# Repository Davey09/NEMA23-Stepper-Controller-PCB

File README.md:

# NEMA 23 Stepper Motor Controller — Arduino-Compatible PCB

A compact, single-axis **12 V bipolar stepper motor controller** that combines an **ATmega328 microcontroller** (Arduino Uno–compatible), a **Trinamic TMC2209** silent stepper driver and an **FT232RL USB-C serial interface** on one 61 × 52 mm two-layer board.

The board is intended as a self-contained joint controller: one board drives one motor, and several boards can be networked over UART to coordinate a multi-axis machine such as a robotic arm. It was designed as the joint electronics for the [5-DOF Cycloidal Drive Robotic Arm](https://github.com/Davey09/Cycloidal-Drive-Robotic-Arm).

| Top | Bottom |
|:---:|:---:|
|  |  |

---

## Key Features

- **Arduino-compatible MCU:** ATmega328 (TQFP-32) with a 16 MHz crystal, so it can be programmed from the Arduino IDE with standard libraries such as *AccelStepper* and *TMCStepper*
- **TMC2209 stepper driver:** up to 2 A RMS, StealthChop2 silent operation, 256-step microstep interpolation and a single-wire UART configuration interface
- **Hardware current setting:** a VREF divider (R16/R17) gives a default limit of about **1.35 A RMS** with no firmware configuration needed
- **USB-C serial bridge:** FT232RL USB-to-UART with DTR auto-reset for bootloader uploads, plus TX/RX activity LEDs
- **Robust power input:** 12 V screw terminal with a US1G series diode for **reverse-polarity protection** and an NCP1117 5 V LDO for the logic rail
- **Expansion I/O:** two filtered digital and two filtered analog 3-pin headers (signal / 5 V / GND) for limit switches, encoders or sensors
- **ICSP header** for flashing the bootloader or firmware directly
- **Manual reset button** and status LEDs
- **2 × M3 mounting holes** for installation inside a joint housing or controller chassis

## Specifications

| Parameter | Value |
|---|---|
| Supply voltage | 12 V DC (motor rail), 5 V regulated logic |
| Microcontroller | ATmega328-A, 16 MHz, 5 V |
| Motor driver | TMC2209-LA (VQFN-28, thermal-via pad) |
| Motor type | 2-phase bipolar stepper (NEMA 14 / 17 / 23) |
| Default phase current | ≈ 1.35 A RMS (hardware VREF); up to 2 A RMS via UART/VREF |
| Microstepping | 1/8 hardware default (MS1 = MS2 = GND), interpolated to 1/256 |
| Chopper mode | StealthChop2 (SPREAD = GND) |
| Current-sense resistors | 0.11 Ω |
| Host interface | USB-C (USB 2.0 full speed) through FT232RL |
| Board size | 61.2 × 52.1 mm |
| Layers | 2 (F.Cu / B.Cu), 1.6 mm FR-4 |
| Components | Mostly SMD (0805 passives), through-hole connectors |
| EDA tool | KiCad 9 |

## Circuit Description

The schematic is a hierarchical design with three sheets:

| Sheet | File | Function |
|---|---|---|
| Main | `Stepper_Controller.kicad_sch` | MCU, motor driver, USB-UART, I/O headers, LEDs |
| Power input | `Power_Supply.kicad_sch` | 12 V input, reverse-polarity protection, 5 V regulation |
| Current reference | `Current_Reference.kicad_sch` | TMC2209 VREF divider |

### Power supply
The 12 V input (J6) passes through **D1 (US1G)**, which blocks current if the supply is connected backwards. The protected 12 V rail feeds the TMC2209 motor supply (VS) directly, with 4.7 µF tantalum, 100 µF and 100 nF bulk and decoupling capacitors next to the driver. An **NCP1117-5.0 LDO (U2)** produces the 5 V `VCC` rail for the MCU, the FT232RL I/O and the expansion headers.

### Microcontroller
The **ATmega328 (U1)** runs from a 16 MHz crystal (Y1) with 22 pF load capacitors and has 100 nF decoupling on each supply pin, AVCC and AREF. RESET has a 10 kΩ pull-up, a tactile reset switch (SW1) and a 100 nF DTR-coupled capacitor, so the bootloader auto-resets the same way it does on an Arduino Uno.

### Stepper driver
The **TMC2209 (U5)** is wired for STEP/DIR control from the MCU:

| TMC2209 pin | Net | ATmega328 pin | Arduino pin |
|---|---|---|---|
| STEP | `STEP` | PD7 | D7 |
| DIR | `DIR` | PD6 | D6 |
| EN (active low) | `ENA` | PD5 | D5 |
| PDN_UART | `UART` | PD2 | D2 |

- **Motor current** is set by VREF. The divider from the driver's internal 5 V output (R16 = 10 kΩ, R17 = 6.2 kΩ, filtered by C14) gives VREF ≈ 1.91 V. With 0.11 Ω sense resistors:
  `I_RMS = (VREF / 2.5 V) × 0.325 V / (R_sense + 0.02 Ω) / √2 ≈ 1.35 A`
- **Microstepping:** MS1 and MS2 are tied low, which selects 1/8 stepping with internal interpolation to 1/256 for very smooth, quiet motion.
- **SPREAD** is tied low, so the driver runs in StealthChop2 for silent operation at low and medium speeds.
- **PDN_UART** connects to an MCU pin, so firmware can override the hardware defaults over the TMC2209 single-wire UART (run current, microstep resolution, StallGuard, CoolStep).
- The motor phases (OA1/OA2, OB1/OB2) go to a 4-way 5.08 mm screw terminal (**J7**).

### USB interface
A **USB-C receptacle (J9)** with 5.1 kΩ CC pull-downs (so the board is recognised as a sink) connects to the **FT232RL (U3)**. TXD/RXD cross over to the ATmega's hardware UART (PD0/PD1), and DTR drives the auto-reset circuit. CBUS0/CBUS1 drive the TX/RX activity LEDs.

### Expansion headers and indicators
| Header | Silkscreen | MCU signal | Notes |
|---|---|---|---|
| J3 | DG_1 | D3 (PD3, INT1 / PWM) | 1 kΩ + 160 nF RC filter |
| J4 | DG_2 | D4 (PD4) | 1 kΩ + 160 nF RC filter |
| J5 | AN_1 | A0 (PC0) | 1 kΩ + 160 nF RC filter |
| J8 | AN_2 | A1 (PC1) | 1 kΩ + 160 nF RC filter |
| J2 | ISP | — | 2 × 3 ICSP programming header |

Each 3-pin header provides **signal / 5 V / GND**, so sensors and switches plug in directly. The RC filters debounce mechanical limit switches and suppress noise coupled from the motor wiring.

LEDs show 5 V power, the D13 status signal and USB TX/RX activity.

## Repository Structure

```
├── hardware/                     KiCad 9 project (open Stepper_Controller.kicad_pro)
│   ├── Stepper_Controller.kicad_pro
│   ├── Stepper_Controller.kicad_sch
│   ├── Stepper_Controller.kicad_pcb
│   ├── Power_Supply.kicad_sch
│   └── Current_Reference.kicad_sch
├── fabrication/
│   ├── Stepper_Controller_Gerbers.zip   Gerber + Excellon drill files (ready for JLCPCB / PCBWay)
│   └── BOM.csv                          Bill of materials
├── docs/
│   └── Schematic.pdf                    Full schematic, all sheets
└── images/                              3D renders
```

## Getting Started

1. **Open the design:** install [KiCad 9](https://www.kicad.org/) and open `hardware/Stepper_Controller.kicad_pro`.
2. **Order PCBs:** upload `fabrication/Stepper_Controller_Gerbers.zip` to any PCB manufacturer (2 layers, 1.6 mm, default settings).
3. **Assemble** the board using `fabrication/BOM.csv`.
4. **Burn the bootloader** through the ICSP header using *Arduino as ISP* or a USBasp, with board type **Arduino Uno**.
5. **Upload firmware** over USB-C from the Arduino IDE. A minimal test:

```cpp
#include <AccelStepper.h>

constexpr uint8_t STEP_PIN = 7, DIR_PIN = 6, EN_PIN = 5;
AccelStepper stepper(AccelStepper::DRIVER, STEP_PIN, DIR_PIN);

void setup() {
  pinMode(EN_PIN, OUTPUT);
  digitalWrite(EN_PIN, LOW);        // enable TMC2209 (active low)
  stepper.setMaxSpeed(4000);        // microsteps/s (1/8 stepping => 1600 steps/rev)
  stepper.setAcceleration(2000);
  stepper.moveTo(1600 * 5);         // 5 motor revolutions
}

void loop() {
  if (stepper.distanceToGo() == 0) stepper.moveTo(-stepper.currentPosition());
  stepper.run();
}
```

## Revision Notes (Rev A)

These items were found in design review and are planned for Rev B:

- **ICSP header mapping:** J2 pins 1 and 4 (MISO/MOSI) are joined to each other and not connected to the MCU, and pin 3 (SCK) goes to PB4 (MISO). Route J2 to PB4/PB3/PB5 as in the standard AVR 6-pin ICSP pinout.
- **FT232RL supply:** the FT232RL VCC pin (20) and the USB-C VBUS pins are not connected. Supply VCC from VBUS or the 5 V rail and add the 3V3OUT decoupling capacitor.
- **TMC2209 clock:** Y2 is a passive crystal on the CLK pin, but the TMC2209 accepts only an external clock signal or GND (internal oscillator). Tie CLK to GND and remove Y2.
- **C13 (100 µF):** this value is not practical in an 0805 package at a 16 V+ rating. Move it to a 1210 MLCC or an electrolytic footprint.

## Roadmap

- Rev B with the fixes above
- Firmware for TMC2209 UART configuration and StallGuard sensorless homing
- Multi-board UART/RS-485 network for coordinated multi-axis motion
- Optional magnetic encoder header for closed-loop position feedback

## Related Project

This controller provides the joint electronics for the **[5-DOF Cycloidal Drive Robotic Arm](https://github.com/Davey09/Cycloidal-Drive-Robotic-Arm)**.

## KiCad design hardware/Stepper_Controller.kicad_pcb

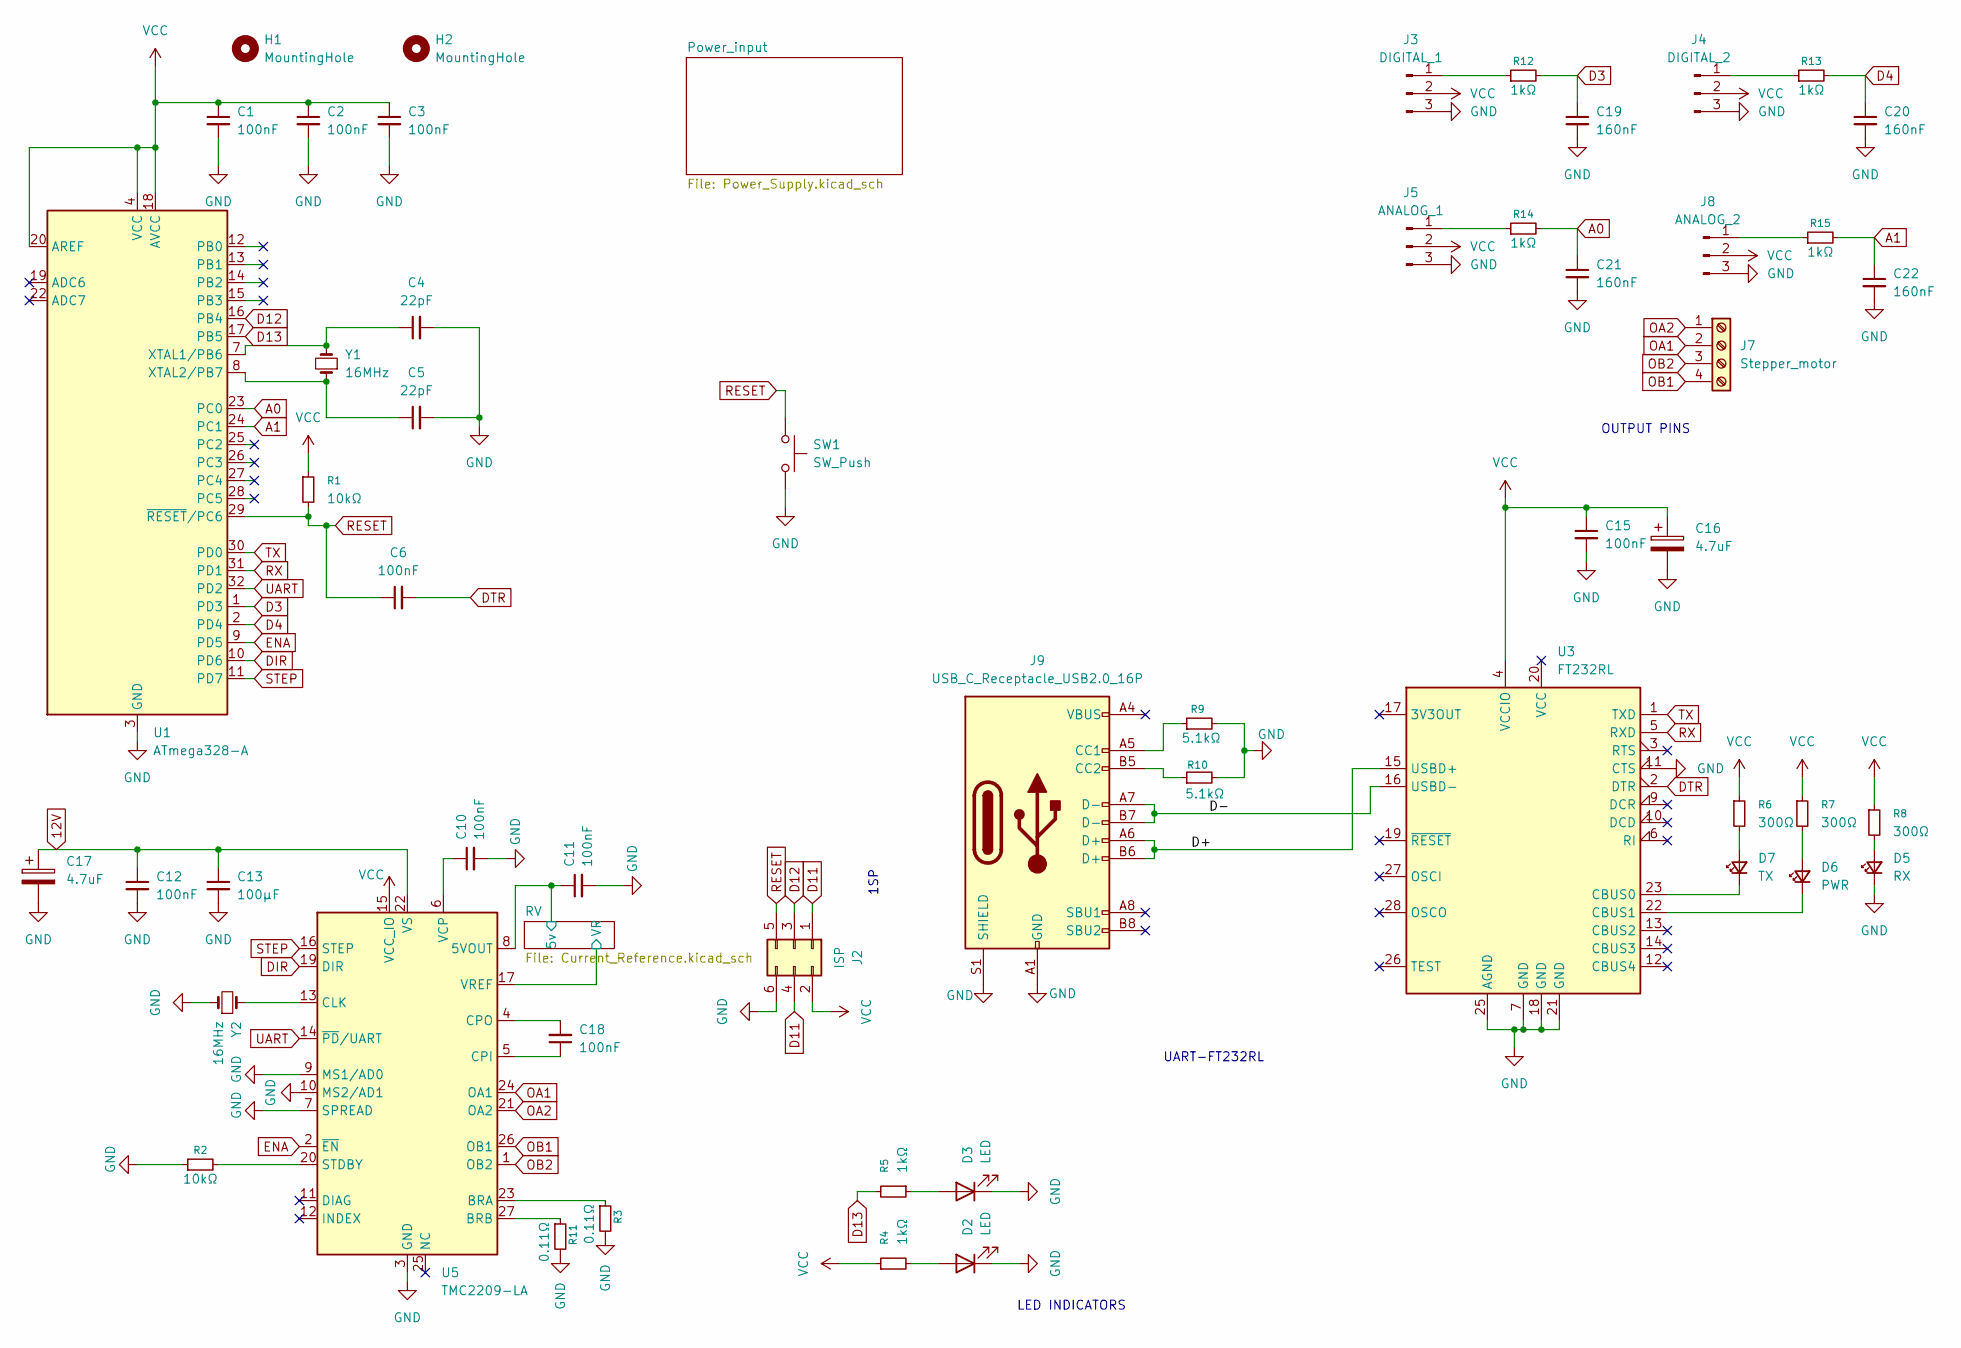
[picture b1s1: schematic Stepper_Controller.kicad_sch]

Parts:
C1, C2, C3, C6, C10, C11, C12, C15, C18: 100nF; C_0805_2012Metric
C4, C5: 22pF; C_0805_2012Metric
C13: 100μF; C_0805_2012Metric
C16, C17: 4.7uF; CP_EIA-3528-15_AVX-H
C19, C20, C21, C22: 160nF; C_0805_2012Metric
D2, D3: LED; LED_0805_2012Metric
D5: RX; LED_0805_2012Metric
D6: PWR; LED_0805_2012Metric
D7: TX; LED_0805_2012Metric
H1, H2: MountingHole; MountingHole_3.2mm_M3_DIN965_Pad
J2: ISP; PinHeader_2x03_P2.54mm_Vertical
J3: DIGITAL_1; PinHeader_1x03_P2.54mm_Vertical
J4: DIGITAL_2; PinHeader_1x03_P2.54mm_Vertical
J5: ANALOG_1; PinHeader_1x03_P2.54mm_Vertical
J7: Stepper_motor; TerminalBlock_Phoenix_MKDS-1,5-4_1x04_P5.00mm_Horizontal
J8: ANALOG_2; PinHeader_1x03_P2.54mm_Vertical
J9: USB_C_Receptacle_USB2.0_16P; USB_C_Receptacle_XKB_U262-16XN-4BVC11
R1, R2: 10kΩ; R_0805_2012Metric
R3, R11: 0.11Ω; R_0805_2012Metric
R4, R5, R12, R13, R14, R15: 1kΩ; R_0805_2012Metric
R6, R7, R8: 300Ω; R_0805_2012Metric
R9, R10: 5.1kΩ; R_0805_2012Metric
SW1: SW_Push; SW_SPST_Omron_B3FS-100xP
U1: ATmega328-A; TQFP-32_7x7mm_P0.8mm
U3: FT232RL; SSOP-28_5.3x10.2mm_P0.65mm
U5: TMC2209-LA; VQFN-28-1EP_5x5mm_P0.5mm_EP3.7x3.7mm_ThermalVias
Y1, Y2: 16MHz; Crystal_HC49-4H_Vertical

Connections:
12V: C12.1, C13.1, C17.1, U5.22 (VS), U5.28 (VS); also elsewhere on the board
/D+: J9.A6 (D+), J9.B6 (D+), U3.15 (USBD+)
/D-: J9.A7 (D-), J9.B7 (D-), U3.16 (USBD-)
/RV/5v: C11.1, U5.8 (5VOUT); also elsewhere on the board
/RV/VR: U5.17 (VREF); also elsewhere on the board
A0: C21.1, R14.2, U1.23 (PC0)
A1: C22.1, R15.2, U1.24 (PC1)
D3: C19.1, R12.2, U1.1 (PD3)
D4: C20.1, R13.2, U1.2 (PD4)
D11: J2.1, J2.4
D12: J2.3, U1.16 (PB4)
D13: R5.2, U1.17 (PB5)
DIR: U1.10 (PD6), U5.19 (DIR)
DTR: C6.2, U3.2 (DTR)
ENA: U1.9 (PD5), U5.2 (~EN)
GND: C1.2, C2.2, C3.2, C4.2, C5.2, C10.2, C11.2, C12.2, C13.2, C15.2, C16.2, C17.2, C19.2, C20.2, C21.2, C22.2, D2.1 (K), D3.1 (K), D5.1 (K), J2.6, J3.3, J4.3, J5.3, J8.3, J9.A1 (GND), J9.A12 (GND), J9.B1 (GND), J9.B12 (GND), J9.S1 (SHIELD), R2.1, R3.2, R9.2, R10.2, R11.2, SW1.2, U1.3 (GND), U1.5 (GND), U1.21 (GND), U3.7 (GND), U3.11 (CTS), U3.18 (GND), U3.21 (GND), U3.25 (AGND), U5.3 (GND), U5.7 (SPREAD), U5.9 (MS1/AD0), U5.10 (MS2/AD1), U5.18 (GND), U5.29 (GND), Y2.1; also elsewhere on the board
unnamed: D2.2 (A), R4.2
unnamed: D3.2 (A), R5.1
unnamed: D5.2 (A), R8.2
unnamed: D6.2 (A), R7.2
unnamed: D6.1 (K), U3.22 (CBUS1)
unnamed: D7.2 (A), R6.2
unnamed: D7.1 (K), U3.23 (CBUS0)
unnamed: J3.1, R12.1
unnamed: J4.1, R13.1
unnamed: J5.1, R14.1
unnamed: J8.1, R15.1
unnamed: J9.A5 (CC1), R9.1
unnamed: J9.B5 (CC2), R10.1
unnamed: C4.1, U1.7 (XTAL1/PB6), Y1.2
unnamed: C5.1, U1.8 (XTAL2/PB7), Y1.1
unnamed: R3.1, U5.23 (BRA)
unnamed: R11.1, U5.27 (BRB)
unnamed: U5.13 (CLK), Y2.2
unnamed: C18.1, U5.5 (CPI)
unnamed: C18.2, U5.4 (CPO)
unnamed: R2.2, U5.20 (STDBY)
unnamed: C10.1, U5.6 (VCP)
OA1: J7.2, U5.24 (OA1)
OA2: J7.1, U5.21 (OA2)
OB1: J7.4, U5.26 (OB1)
OB2: J7.3, U5.1 (OB2)
RESET: C6.1, J2.5, R1.2, SW1.1, U1.29 (~RESET/PC6)
RX: U1.31 (PD1), U3.5 (RXD)
STEP: U1.11 (PD7), U5.16 (STEP)
TX: U1.30 (PD0), U3.1 (TXD)
UART: U1.32 (PD2), U5.14 (~PD/UART)
VCC: C1.1, C2.1, C3.1, C15.1, C16.1, J2.2, J3.2, J4.2, J5.2, J8.2, R1.1, R4.1, R6.1, R7.1, R8.1, U1.4 (VCC), U1.6 (VCC), U1.18 (AVCC), U1.20 (AREF), U3.4 (VCCIO), U5.15 (VCC_IO); also elsewhere on the board

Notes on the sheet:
OUTPUT PINS
LED INDICATORS
1SP
UART-FT232RL

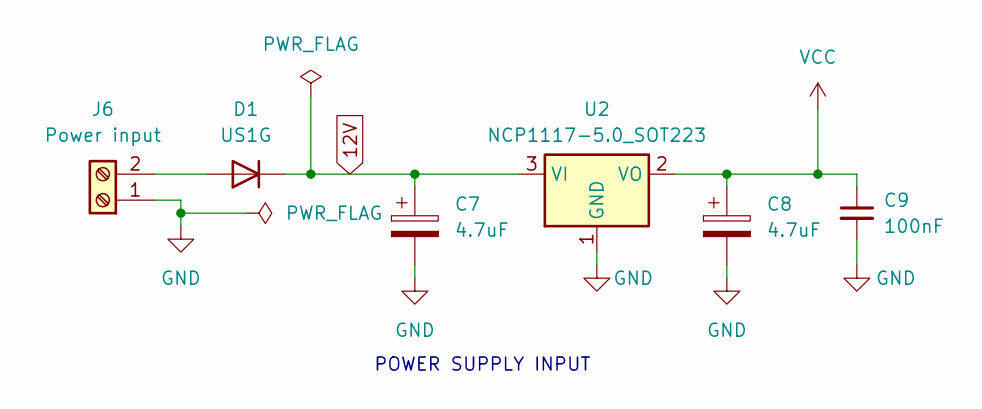
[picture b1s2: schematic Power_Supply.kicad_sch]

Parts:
C7, C8: 4.7uF; CP_EIA-3528-15_AVX-H
C9: 100nF; C_0805_2012Metric
D1: US1G; D_SMA
J6: Power input; TerminalBlock_Phoenix_MPT-0,5-2-2.54_1x02_P2.54mm_Horizontal
U2: NCP1117-5.0_SOT223; SOT-223-3_TabPin2

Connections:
12V: C7.1, D1.1 (K), U2.3 (VI); also elsewhere on the board
GND: C7.2, C8.2, C9.2, J6.1, U2.1 (GND); also elsewhere on the board
unnamed: D1.2 (A), J6.2
VCC: C8.1, C9.1, U2.2 (VO); also elsewhere on the board

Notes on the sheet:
POWER SUPPLY INPUT

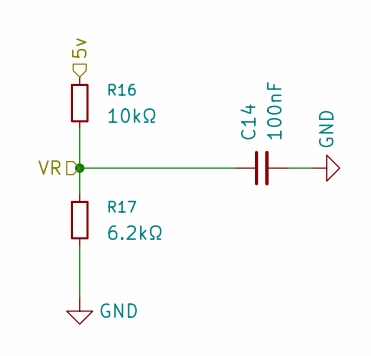
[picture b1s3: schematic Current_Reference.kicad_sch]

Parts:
C14: 100nF; C_0805_2012Metric
R16: 10kΩ; R_0805_2012Metric
R17: 6.2kΩ; R_0805_2012Metric

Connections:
/RV/5v: R16.1; also elsewhere on the board
/RV/VR: C14.1, R16.2, R17.1; also elsewhere on the board
GND: C14.2, R17.2; also elsewhere on the board

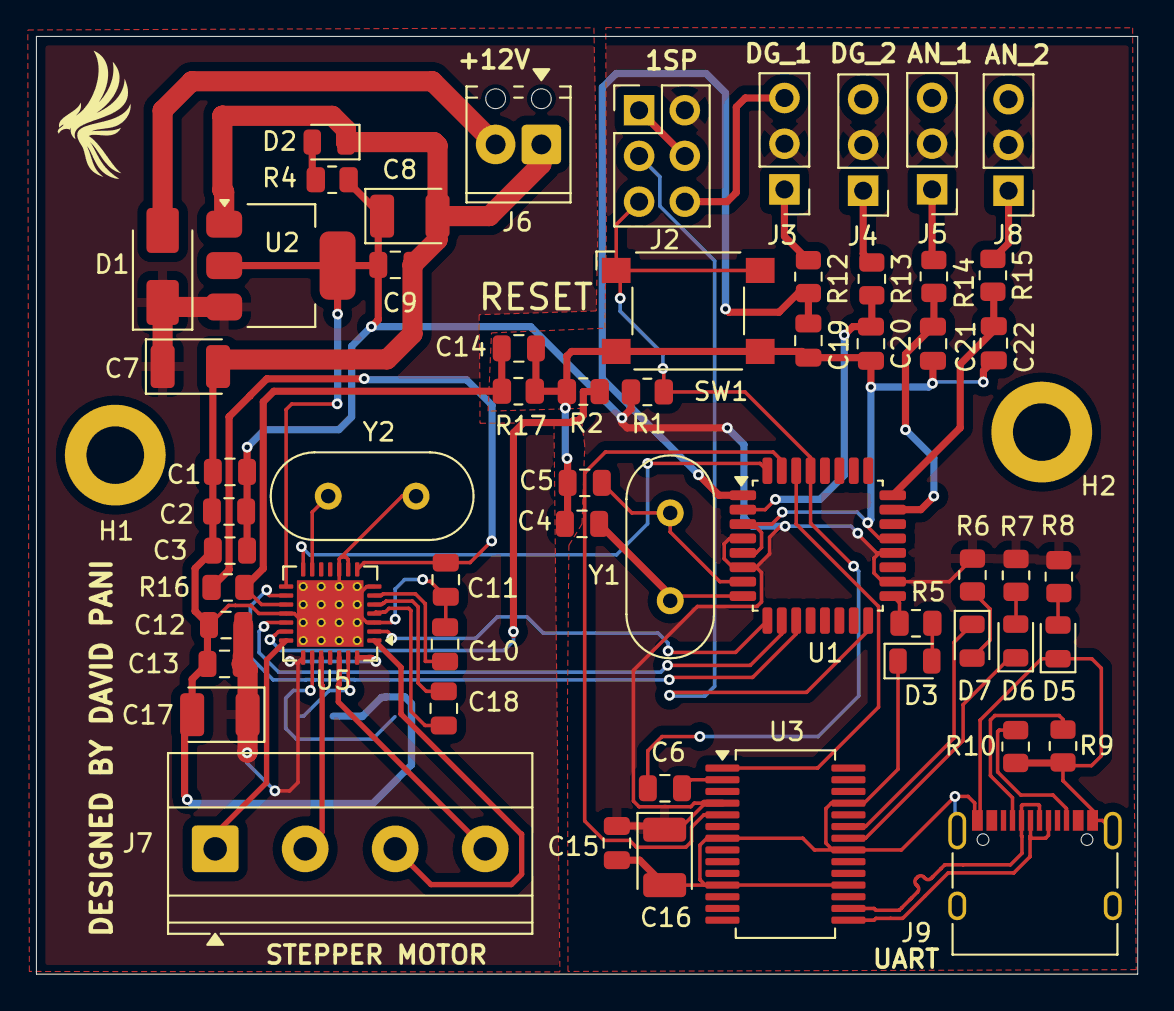
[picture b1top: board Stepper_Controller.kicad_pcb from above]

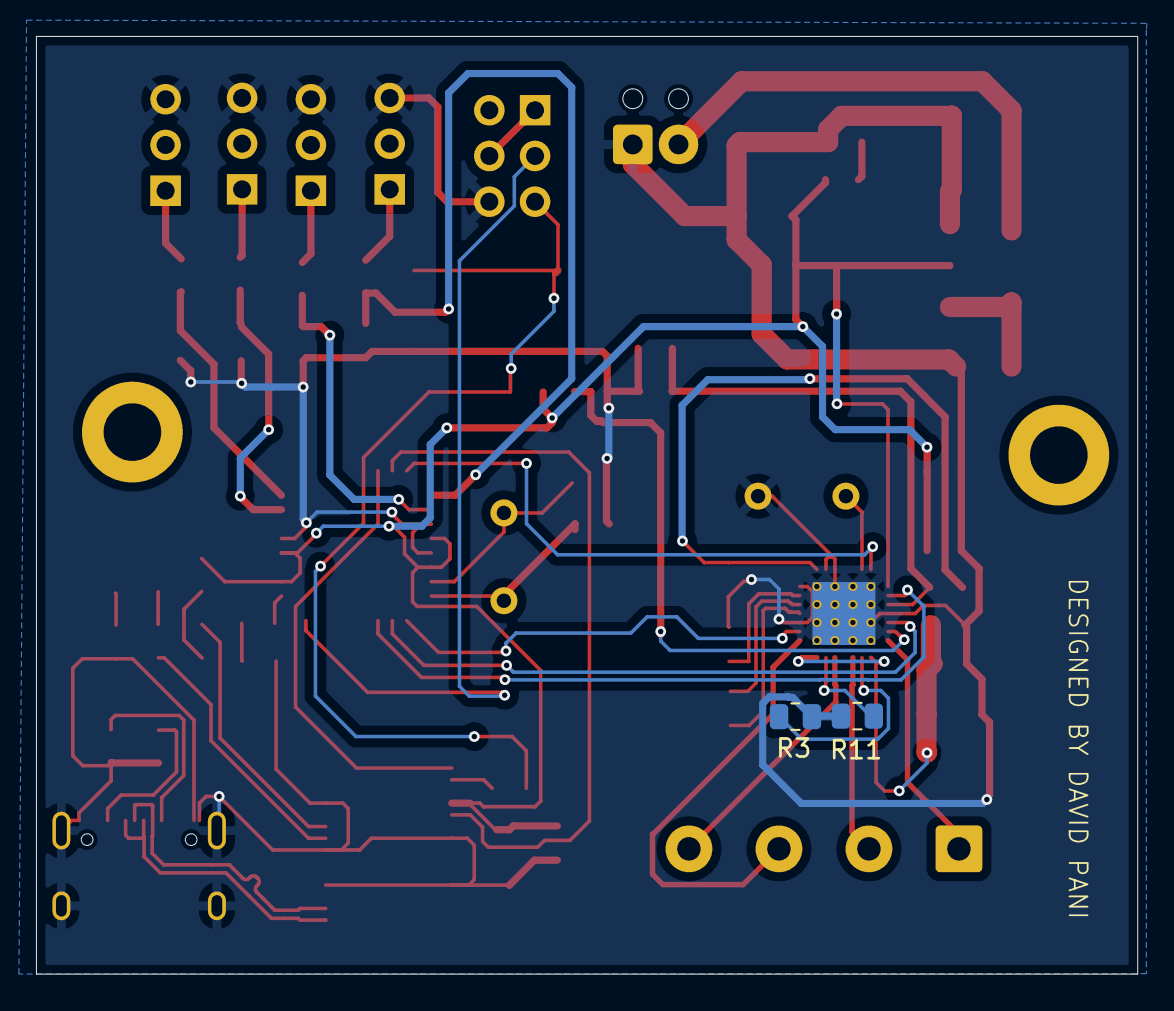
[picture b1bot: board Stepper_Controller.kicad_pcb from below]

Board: 2 copper layers, 61.2 x 52.1 mm, 62 parts (2 on the bottom side), 49 nets.

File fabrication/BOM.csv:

"Reference","Value","Footprint","Qty"
"C1-C3,C6,C9-C12,C14,C15,C18","100nF","Capacitor_SMD:C_0805_2012Metric","11"
"C4,C5","22pF","Capacitor_SMD:C_0805_2012Metric","2"
"C7,C8,C16,C17","4.7uF","Capacitor_Tantalum_SMD:CP_EIA-3528-15_AVX-H","4"
"C13","100μF","Capacitor_SMD:C_0805_2012Metric","1"
"C19-C22","160nF","Capacitor_SMD:C_0805_2012Metric","4"
"D1","US1G","Diode_SMD:D_SMA","1"
"D2,D3","LED","LED_SMD:LED_0805_2012Metric","2"
"D5","RX","LED_SMD:LED_0805_2012Metric","1"
"D6","PWR","LED_SMD:LED_0805_2012Metric","1"
"D7","TX","LED_SMD:LED_0805_2012Metric","1"
"J2","ISP","Connector_PinHeader_2.54mm:PinHeader_2x03_P2.54mm_Vertical","1"
"J3","DIGITAL_1","Connector_PinHeader_2.54mm:PinHeader_1x03_P2.54mm_Vertical","1"
"J4","DIGITAL_2","Connector_PinHeader_2.54mm:PinHeader_1x03_P2.54mm_Vertical","1"
"J5","ANALOG_1","Connector_PinHeader_2.54mm:PinHeader_1x03_P2.54mm_Vertical","1"
"J6","Power input","TerminalBlock_Phoenix:TerminalBlock_Phoenix_MPT-0,5-2-2.54_1x02_P2.54mm_Horizontal","1"
"J7","Stepper_motor","TerminalBlock_Phoenix:TerminalBlock_Phoenix_MKDS-1,5-4_1x04_P5.00mm_Horizontal","1"
"J8","ANALOG_2","Connector_PinHeader_2.54mm:PinHeader_1x03_P2.54mm_Vertical","1"
"J9","USB_C_Receptacle_USB2.0_16P","Connector_USB:USB_C_Receptacle_XKB_U262-16XN-4BVC11","1"
"R1,R2,R16","10kΩ","Resistor_SMD:R_0805_2012Metric","3"
"R3,R11","0.11Ω","Resistor_SMD:R_0805_2012Metric","2"
"R4,R5,R12-R15","1kΩ","Resistor_SMD:R_0805_2012Metric","6"
"R6-R8","300Ω","Resistor_SMD:R_0805_2012Metric","3"
"R9,R10","5.1kΩ","Resistor_SMD:R_0805_2012Metric","2"
"R17","6.2kΩ","Resistor_SMD:R_0805_2012Metric","1"
"SW1","SW_Push","Button_Switch_SMD:SW_SPST_Omron_B3FS-100xP","1"
"U1","ATmega328-A","Package_QFP:TQFP-32_7x7mm_P0.8mm","1"
"U2","NCP1117-5.0_SOT223","Package_TO_SOT_SMD:SOT-223-3_TabPin2","1"
"U3","FT232RL","Package_SO:SSOP-28_5.3x10.2mm_P0.65mm","1"
"U5","TMC2209-LA","Package_DFN_QFN:VQFN-28-1EP_5x5mm_P0.5mm_EP3.7x3.7mm_ThermalVias","1"
"Y1,Y2","16MHz","Crystal:Crystal_HC49-4H_Vertical","2"
